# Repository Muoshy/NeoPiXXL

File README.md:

# NeoPiXXL
XXL version of the classic WS2812B/NeoPixel with same functionality.

## Assembly

iBOM for driver assembly can be found here: https://muoshy.github.io/NeoPiXXL/ 

### BOM:
 - Driver:
    - PCB
    - WS2811
    - 33 ohm 0603 resistor x2
    - 100 ohm 0603 resistor
    - 100 nF 0603 capacitor
 - Plate:
    - PCB
    - Red LED
    - Green LED
    - Blue LED
 - Hardware:
    - Bottom plate (3D printed)
    - Top plate (vacuum formed)

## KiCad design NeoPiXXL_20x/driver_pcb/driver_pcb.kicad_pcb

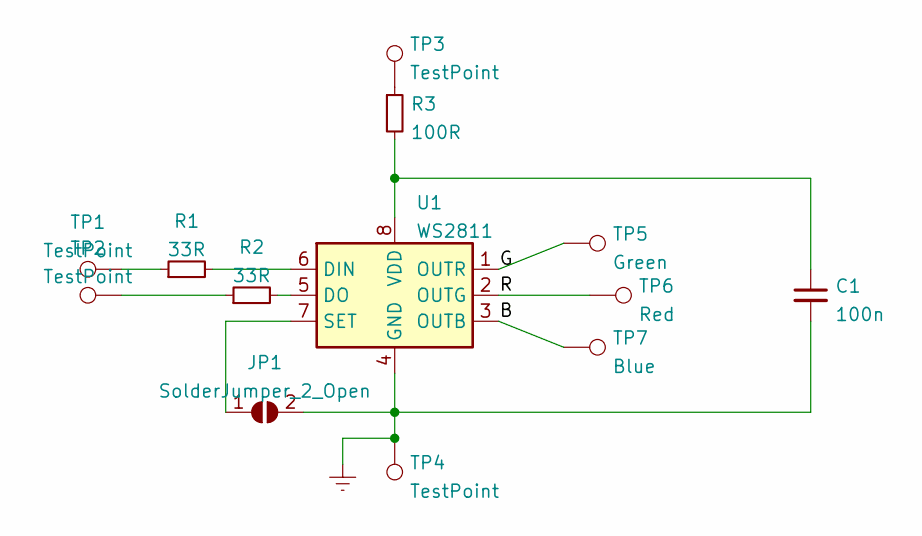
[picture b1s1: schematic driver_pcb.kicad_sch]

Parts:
C1: 100n; C_0603_1608Metric_Pad1.08x0.95mm_HandSolder
JP1: SolderJumper_2_Open; SolderJumper-2_P1.3mm_Open_TrianglePad1.0x1.5mm
R1, R2: 33R; R_0603_1608Metric_Pad0.98x0.95mm_HandSolder
R3: 100R; R_0603_1608Metric_Pad0.98x0.95mm_HandSolder
TP1, TP2, TP3, TP4: TestPoint; WirePad
TP5: Green; WirePad
TP6: Red; WirePad
TP7: Blue; WirePad
U1: WS2811; SOIC-8_3.9x4.9mm_P1.27mm

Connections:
/B: TP7.1, U1.3 (OUTB)
/G: TP5.1, U1.1 (OUTR)
/R: TP6.1, U1.2 (OUTG)
Earth: C1.2, JP1.2 (B), TP4.1, U1.4 (GND)
unnamed: C1.1, R3.2, U1.8 (VDD)
unnamed: JP1.1 (A), U1.7 (SET)
unnamed: R1.1, TP1.1
unnamed: R1.2, U1.6 (DIN)
unnamed: R2.1, TP2.1
unnamed: R2.2, U1.5 (DO)
unnamed: R3.1, TP3.1

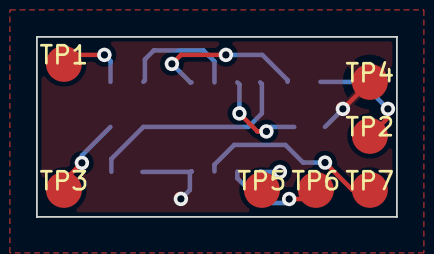
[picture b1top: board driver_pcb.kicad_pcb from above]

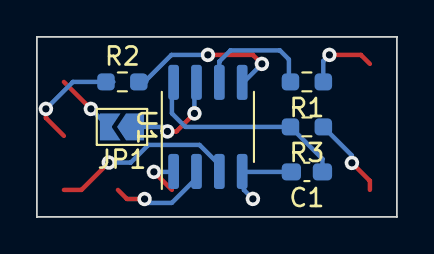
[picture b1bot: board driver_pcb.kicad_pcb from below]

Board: 2 copper layers, 20.0 x 10.0 mm, 13 parts (6 on the bottom side), 11 nets.

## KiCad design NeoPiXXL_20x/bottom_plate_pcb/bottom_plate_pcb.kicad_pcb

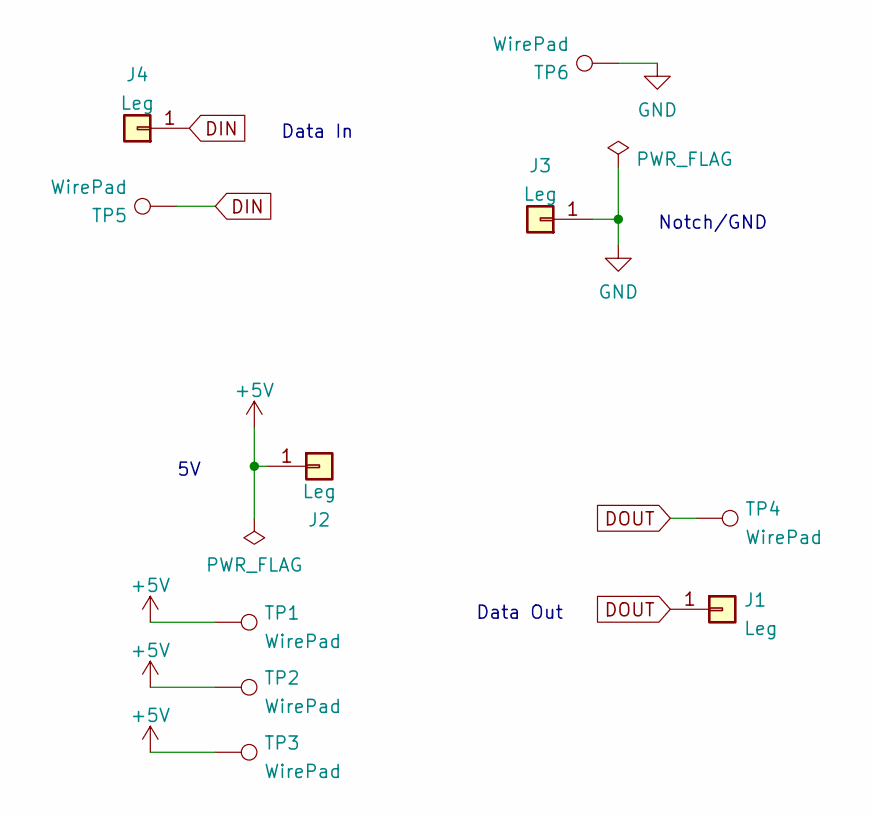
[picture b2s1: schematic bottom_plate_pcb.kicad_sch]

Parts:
J1, J2, J3, J4: Leg; pin_pad
TP1, TP2, TP3, TP4, TP5, TP6: WirePad

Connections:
+5V: J2.1, TP1.1, TP2.1, TP3.1
DIN: J4.1, TP5.1
DOUT: J1.1, TP4.1
GND: J3.1, TP6.1

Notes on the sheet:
Data In
Data Out
Notch/GND

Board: 2 copper layers, 10 parts (0 on the bottom side), 4 nets, no tracks yet.

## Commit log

2022-06-15 Added reference images
2022-06-15 Reference images
2022-06-15 Added svg for copper pour pattern
2022-06-16 added bottom plate pcb
2022-06-16 Driver IC (simple)
2022-06-17 add mounting holes to bottom plate
2022-06-20 fixed DOUT/DIN swap for 20x variant
2022-06-20 add gitignore
2022-08-05 include BOM
2022-09-08 STL files
2022-09-08 Added BOM
2022-09-08 Update driver for correct LED placement
